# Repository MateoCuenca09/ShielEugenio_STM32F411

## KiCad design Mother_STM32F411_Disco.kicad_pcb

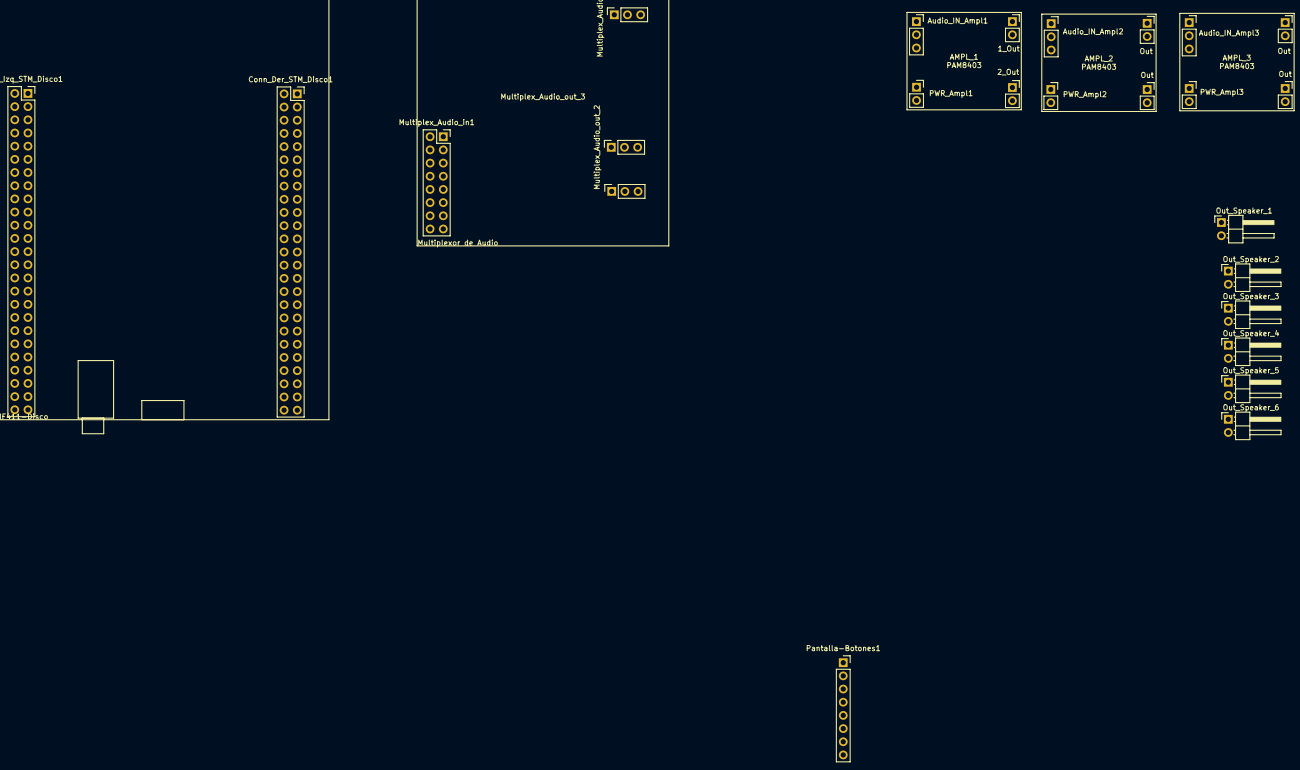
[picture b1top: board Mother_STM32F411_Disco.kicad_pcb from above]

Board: 2 copper layers, 25 parts (0 on the bottom side), 45 nets, no tracks yet.

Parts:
1_Out, 2_Out: Conn_01x02; PinSocket_1x02_P2.54mm_Vertical
Audio_IN_Ampl1, Audio_IN_Ampl2, Audio_IN_Ampl3: Conn_01x03; PinSocket_1x03_P2.54mm_Vertical
Conn_Der_STM_Disco1: Conn_02x25_Odd_Even; PinSocket_2x25_P2.54mm_Vertical
Conn_Izq_STM_Disco1: Conn_02x25_Odd_Even; PinSocket_2x25_P2.54mm_Vertical
Multiplex_Audio_in1: Conn_02x08_Counter_Clockwise; PinSocket_2x08_P2.54mm_Vertical
Multiplex_Audio_out_1, Multiplex_Audio_out_2, Multiplex_Audio_out_3: Conn_01x03; PinSocket_1x03_P2.54mm_Vertical
Out: Conn_01x02; PinSocket_1x02_P2.54mm_Vertical
Out#2, Out#3, Out#4: Conn_01x02; PinSocket_1x02_P2.54mm_Vertical
Out_Speaker_1, Out_Speaker_2, Out_Speaker_3, Out_Speaker_4, Out_Speaker_5, Out_Speaker_6: Conn_01x02; PinHeader_1x02_P2.54mm_Horizontal
PWR_Ampl1, PWR_Ampl2, PWR_Ampl3: Conn_01x02; PinSocket_1x02_P2.54mm_Vertical
Pantalla-Botones1: Conn_01x08; PinSocket_1x08_P2.54mm_Vertical

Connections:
/3V: Conn_Der_STM_Disco1.5, Conn_Der_STM_Disco1.6
/5V: Conn_Der_STM_Disco1.3, Conn_Der_STM_Disco1.4, Pantalla-Botones1.8
/GND: Conn_Der_STM_Disco1.1, Conn_Der_STM_Disco1.2, Conn_Der_STM_Disco1.49, Conn_Der_STM_Disco1.50, Conn_Izq_STM_Disco1.1, Conn_Izq_STM_Disco1.2, Conn_Izq_STM_Disco1.5, Conn_Izq_STM_Disco1.23, Conn_Izq_STM_Disco1.49, Conn_Izq_STM_Disco1.50, Multiplex_Audio_in1.2, PWR_Ampl1.1, PWR_Ampl2.1, PWR_Ampl3.1, Pantalla-Botones1.1
/NC: Conn_Izq_STM_Disco1.35, Conn_Izq_STM_Disco1.48
/NRST: Conn_Izq_STM_Disco1.6, Multiplex_Audio_in1.15
/PA0: Conn_Izq_STM_Disco1.12, Multiplex_Audio_in1.12
/PA1: Conn_Izq_STM_Disco1.11, Multiplex_Audio_in1.5
/PA2: Conn_Izq_STM_Disco1.14, Multiplex_Audio_in1.11
/PA3: Conn_Izq_STM_Disco1.13, Multiplex_Audio_in1.6
/PA4: Conn_Izq_STM_Disco1.16, Multiplex_Audio_in1.10
/PA5: Conn_Izq_STM_Disco1.15, Multiplex_Audio_in1.7
/PA6: Conn_Izq_STM_Disco1.18, Multiplex_Audio_in1.9
/PA7: Conn_Izq_STM_Disco1.17, Multiplex_Audio_in1.8
/PA8: Conn_Der_STM_Disco1.43, Pantalla-Botones1.6
/PC0: Conn_Izq_STM_Disco1.8, Multiplex_Audio_in1.14
/PC1: Conn_Izq_STM_Disco1.7, Multiplex_Audio_in1.3
/PC2: Conn_Izq_STM_Disco1.10, Multiplex_Audio_in1.13
/PC3: Conn_Izq_STM_Disco1.9, Multiplex_Audio_in1.4
/PC9: Conn_Der_STM_Disco1.46, Pantalla-Botones1.7
/PD9: Conn_Izq_STM_Disco1.41, Pantalla-Botones1.5
/PD11: Conn_Izq_STM_Disco1.43, Pantalla-Botones1.4
/PD13: Conn_Izq_STM_Disco1.45, Pantalla-Botones1.3
/PD14: Conn_Izq_STM_Disco1.46, Pantalla-Botones1.2
/VDD: Conn_Der_STM_Disco1.22, Conn_Izq_STM_Disco1.3, Conn_Izq_STM_Disco1.4, Multiplex_Audio_in1.1, Multiplex_Audio_in1.16, PWR_Ampl1.2, PWR_Ampl2.2, PWR_Ampl3.2
unnamed: 1_Out.1, Out_Speaker_1.2
unnamed: 1_Out.2, Out_Speaker_1.1
unnamed: Out#2.1, Out_Speaker_3.2
unnamed: Out#2.2, Out_Speaker_3.1
unnamed: Out#3.1, Out_Speaker_5.2
unnamed: Out#3.2, Out_Speaker_5.1
unnamed: 2_Out.1, Out_Speaker_2.2
unnamed: 2_Out.2, Out_Speaker_2.1
unnamed: Out#4.1, Out_Speaker_4.2
unnamed: Out#4.2, Out_Speaker_4.1
unnamed: Out.1, Out_Speaker_6.2
unnamed: Out.2, Out_Speaker_6.1
unnamed: Audio_IN_Ampl1.1, Multiplex_Audio_out_1.3
unnamed: Audio_IN_Ampl1.2, Multiplex_Audio_out_1.1
unnamed: Audio_IN_Ampl1.3, Multiplex_Audio_out_1.2
unnamed: Audio_IN_Ampl2.1, Multiplex_Audio_out_2.3
unnamed: Audio_IN_Ampl2.2, Multiplex_Audio_out_2.1
unnamed: Audio_IN_Ampl2.3, Multiplex_Audio_out_2.2
unnamed: Audio_IN_Ampl3.1, Multiplex_Audio_out_3.3
unnamed: Audio_IN_Ampl3.2, Multiplex_Audio_out_3.1
unnamed: Audio_IN_Ampl3.3, Multiplex_Audio_out_3.2

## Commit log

2025-05-09 add modules in schematic
2025-05-30 Huellas y netlist
2025-05-30 Huellas prearmadas, falta comprobar medidas
